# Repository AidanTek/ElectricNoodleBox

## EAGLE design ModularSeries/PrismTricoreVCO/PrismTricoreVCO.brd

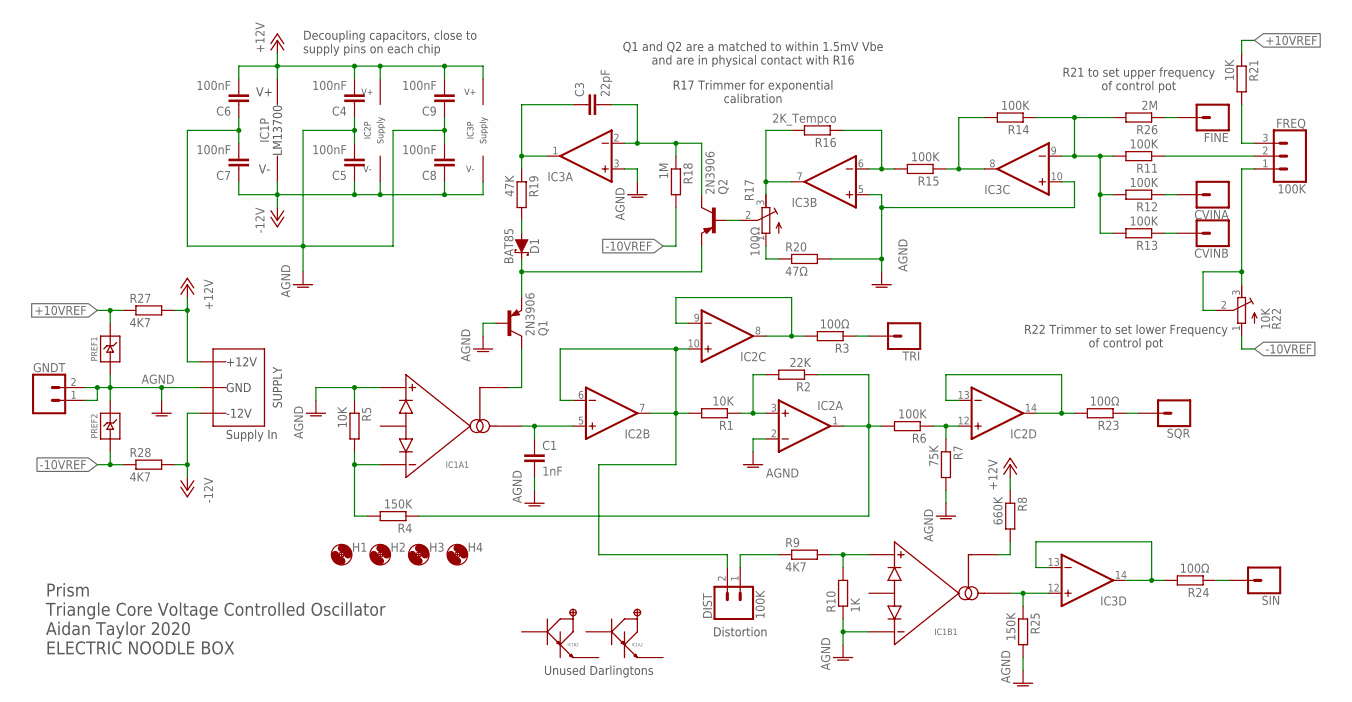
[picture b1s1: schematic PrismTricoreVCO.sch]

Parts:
C1: 1nF; C050-025X075
C3: 22pF; C050-025X075
C4, C5, C6, C7, C8, C9: 100nF; C050-025X075
CVINA: 1XWIREPAD; 1X01
CVINB: 1XWIREPAD; 1X01
D1: BAT85; DO35-7
DIST: 100K; 1X02
FINE: 1XWIREPAD; 1X01
FREQ: 100K; 1X03
GNDT: 2XWIREPAD; 1X02
H1, H2, H3, H4: MOUNT-HOLE3.2; 3,2
IC1: LM13700DIL; DIL16
IC2, IC3: TL0X4DIL; DIL14
PREF1, PREF2: LM4040TH; TO92
Q1, Q2: 2N3906; TO92
R1, R5, R21: 10K; 0207/10
R2: 22K; 0207/10
R3, R23, R24: 100Ω; 0207/10
R4, R25: 150K; 0207/10
R6, R11, R12, R13, R14, R15: 100K; 0207/10
R7: 75K; 0207/10
R8: 660K; 0207/10
R9, R27, R28: 4K7; 0207/10
R10: 1K; 0207/10
R16: 2K_Tempco; 0207/10
R17: 100Ω; RTRIM3296W
R18: 1M; 0207/10
R19: 47K; 0207/10
R20: 47Ω; 0207/10
R22: 10K; RTRIM3296W
R26: 2M; 0207/10
SIN: 1XWIREPAD; 1X01
SQR: 1XWIREPAD; 1X01
TRI: 1XWIREPAD; 1X01
WP1: COMBO_SUPPLY_HEADER; COMBINED_POWER

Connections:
+10VREF: PREF1.2 (CATHODE), R21.1, R27.1
+12V: C4.2, C6.2, C9.2, IC1.11 (V+), IC2.4 (V+), IC3.4 (V+), R8.1, R27.2, WP1.V+1 (V++), WP1.V+2 (V++), WP1.V+3 (V++)
-10VREF: PREF2.3 (ANODE), R18.2, R22.1 (A), R28.1
-12V: C5.1, C7.1, C8.1, IC1.6 (V-), IC2.11 (V-), IC3.11 (V-), R28.2, WP1.V-1 (V--), WP1.V-2 (V--), WP1.V-3 (V--)
AGND: C1.2, C4.1, C5.2, C6.1, C7.2, C8.2, C9.1, GNDT.1, GNDT.2, IC1.3 (AMP+), IC1.13 (AMP-), IC2.2 (-IN), IC3.3 (+IN), IC3.5 (+IN), IC3.10 (+IN), PREF1.3 (ANODE), PREF2.2 (CATHODE), Q1.2 (B), R5.1, R7.2, R10.1, R20.2, R25.2, WP1.GND1 (AGND), WP1.GND2 (AGND), WP1.GND3 (AGND), WP1.GND4 (AGND), WP1.GND5 (AGND), WP1.GND6 (AGND), WP1.GND7 (AGND), WP1.GND8 (AGND)
unnamed: DIST.2, IC2.6 (-IN), IC2.7 (OUT), IC2.10 (+IN), R1.2
unnamed: IC2.3 (+IN), R1.1, R2.2
unnamed: C1.1, IC1.5 (AMPOUT), IC2.5 (+IN)
unnamed: IC2.1 (OUT), R2.1, R4.1, R6.2
unnamed: IC2.8 (OUT), IC2.9 (-IN), R3.2
unnamed: IC1.4 (AMP-), R4.2, R5.2
unnamed: IC1.14 (AMP+), R9.2, R10.2
unnamed: IC2.12 (+IN), R6.1, R7.1
unnamed: IC1.12 (AMPOUT), IC3.12 (+IN), R25.1
unnamed: IC1.16 (AMPBIAS), R8.2
unnamed: IC1.1 (AMPBIAS), Q1.1 (C)
unnamed: DIST.1, R9.1
unnamed: IC3.7 (OUT), R16.2, R17.3 (E)
unnamed: IC3.6 (-IN), R15.2, R16.1
unnamed: IC3.8 (OUT), R14.2, R15.1
unnamed: Q2.2 (B), R17.2 (S)
unnamed: C3.2, IC3.2 (-IN), Q2.1 (C), R18.1
unnamed: R17.1 (A), R20.1
unnamed: C3.1, IC3.1 (OUT), R19.1
unnamed: D1.C, Q1.3 (E), Q2.3 (E)
unnamed: D1.A, R19.2
unnamed: IC3.9 (-IN), R11.2, R12.2, R13.2, R14.1, R26.2
unnamed: FREQ.2, R11.1
unnamed: FREQ.1, R22.2 (S), R22.3 (E)
unnamed: FREQ.3, R21.2
unnamed: CVINA.1, R12.1
unnamed: CVINB.1, R13.1
unnamed: R3.1, TRI.1
unnamed: R23.1, SQR.1
unnamed: R24.1, SIN.1
unnamed: FINE.1, R26.1
SINE_OUT: IC3.13 (-IN), IC3.14 (OUT), R24.2
SQUARE_OUT: IC2.13 (-IN), IC2.14 (OUT), R23.2

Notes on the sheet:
Distortion
Unused Darlingtons
R22 Trimmer to set lower Frequency of control pot
R17 Trimmer for exponential calibration
R21 to set upper frequency of control pot
Q1 and Q2 are a matched to within 1.5mV Vbe and are in physical contact with R16
Prism Triangle Core Voltage Controlled Oscillator Aidan Taylor 2020 ELECTRIC NOODLE BOX
Supply In
Decoupling capacitors, close to supply pins on each chip

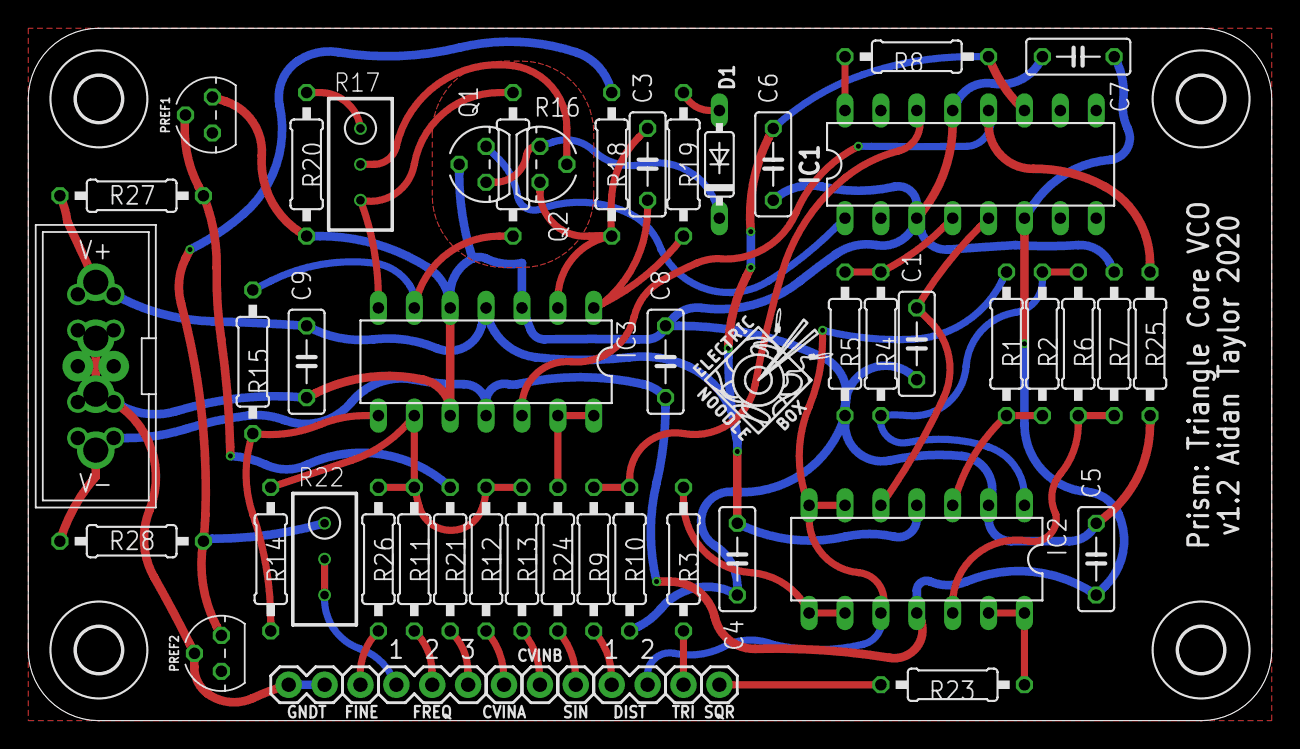
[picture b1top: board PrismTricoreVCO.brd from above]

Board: 2 copper layers, 88.0 x 49.0 mm, 60 parts (1 on the bottom side), 38 nets.

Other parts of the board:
U$1, U$2: LOGO10X10

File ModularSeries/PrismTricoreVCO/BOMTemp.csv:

"Qty";"Value";"Device";"Package";"Parts";"Description";"POPULARITY";"SPICEMODEL";"SPICEPREFIX";"SPICEPREFIXL";
"1";"";"LM13700DIL";"DIL16";"IC1";"";"";"";"";"";
"2";"";"LM4040TH";"TO-92";"PREF1, PREF2";"";"";"";"";"";
"2";"";"TL0X4DIL";"DIL14";"IC2, IC3";"";"";"";"";"";
"1";"100K";"2XWIREPAD";"1X02";"DIST";"";"";"";"";"";
"1";"100K";"3XWIREPAD";"1X03";"FREQ";"";"";"";"";"";
"6";"100K";"R-EU_0207/10";"0207/10";"R6, R11, R12, R13, R14, R15";"RESISTOR, European symbol";"81";"";"R";"";
"6";"100nF";"C-EU050-025X075";"C050-025X075";"C4, C5, C6, C7, C8, C9";"CAPACITOR, European symbol";"29";"";"C";"";
"3";"100Ω";"R-EU_0207/10";"0207/10";"R3, R23, R24";"RESISTOR, European symbol";"81";"";"R";"";
"1";"100Ω";"R-TRIMM3296W";"RTRIM3296W";"R17";"Trimm resistor";"3";"X";"";"POT";
"3";"10K";"R-EU_0207/10";"0207/10";"R1, R5, R21";"RESISTOR, European symbol";"81";"";"R";"";
"1";"10K";"R-TRIMM3296W";"RTRIM3296W";"R22";"Trimm resistor";"3";"X";"";"POT";
"2";"150K";"R-EU_0207/10";"0207/10";"R4, R25";"RESISTOR, European symbol";"81";"";"R";"";
"1";"1K";"R-EU_0207/10";"0207/10";"R10";"RESISTOR, European symbol";"81";"";"R";"";
"1";"1M";"R-EU_0207/10";"0207/10";"R18";"RESISTOR, European symbol";"81";"";"R";"";
"6";"1XWIREPAD";"1XWIREPAD";"1X01";"CVINA, CVINB, FINE, SIN, SQR, TRI";"";"";"";"";"";
"1";"1nF";"C-EU050-025X075";"C050-025X075";"C1";"CAPACITOR, European symbol";"29";"";"C";"";
"1";"22K";"R-EU_0207/10";"0207/10";"R2";"RESISTOR, European symbol";"81";"";"R";"";
"1";"22pF";"C-EU050-025X075";"C050-025X075";"C3";"CAPACITOR, European symbol";"29";"";"C";"";
"1";"2K_Tempco";"R-EU_0207/10";"0207/10";"R16";"RESISTOR, European symbol";"81";"";"R";"";
"1";"2M";"R-EU_0207/10";"0207/10";"R26";"RESISTOR, European symbol";"81";"";"R";"";
"2";"2N3906";"2N3906";"TO92";"Q1, Q2";"PNP Transistor";"11";"";"";"";
"1";"2XWIREPAD";"2XWIREPAD";"1X02";"GNDT";"";"";"";"";"";
"1";"47K";"R-EU_0207/10";"0207/10";"R19";"RESISTOR, European symbol";"81";"";"R";"";
"1";"47Ω";"R-EU_0207/10";"0207/10";"R20";"RESISTOR, European symbol";"81";"";"R";"";
"3";"4K7";"R-EU_0207/10";"0207/10";"R9, R27, R28";"RESISTOR, European symbol";"81";"";"R";"";
"1";"660K";"R-EU_0207/10";"0207/10";"R8";"RESISTOR, European symbol";"81";"";"R";"";
"1";"75K";"R-EU_0207/10";"0207/10";"R7";"RESISTOR, European symbol";"81";"";"R";"";
"1";"BAT85";"SCHOTTKY_DO35";"DO35-7";"D1";"";"";"";"";"";
"1";"COMBO_SUPPLY_HEADER";"COMBO_SUPPLY_HEADER";"COMBINED_POWER";"WP1";"";"";"";"";"";
"4";"MOUNT-HOLE3.2";"MOUNT-HOLE3.2";"3,2";"H1, H2, H3, H4";"MOUNTING HOLE with drill center marker";"7";"";"";"";

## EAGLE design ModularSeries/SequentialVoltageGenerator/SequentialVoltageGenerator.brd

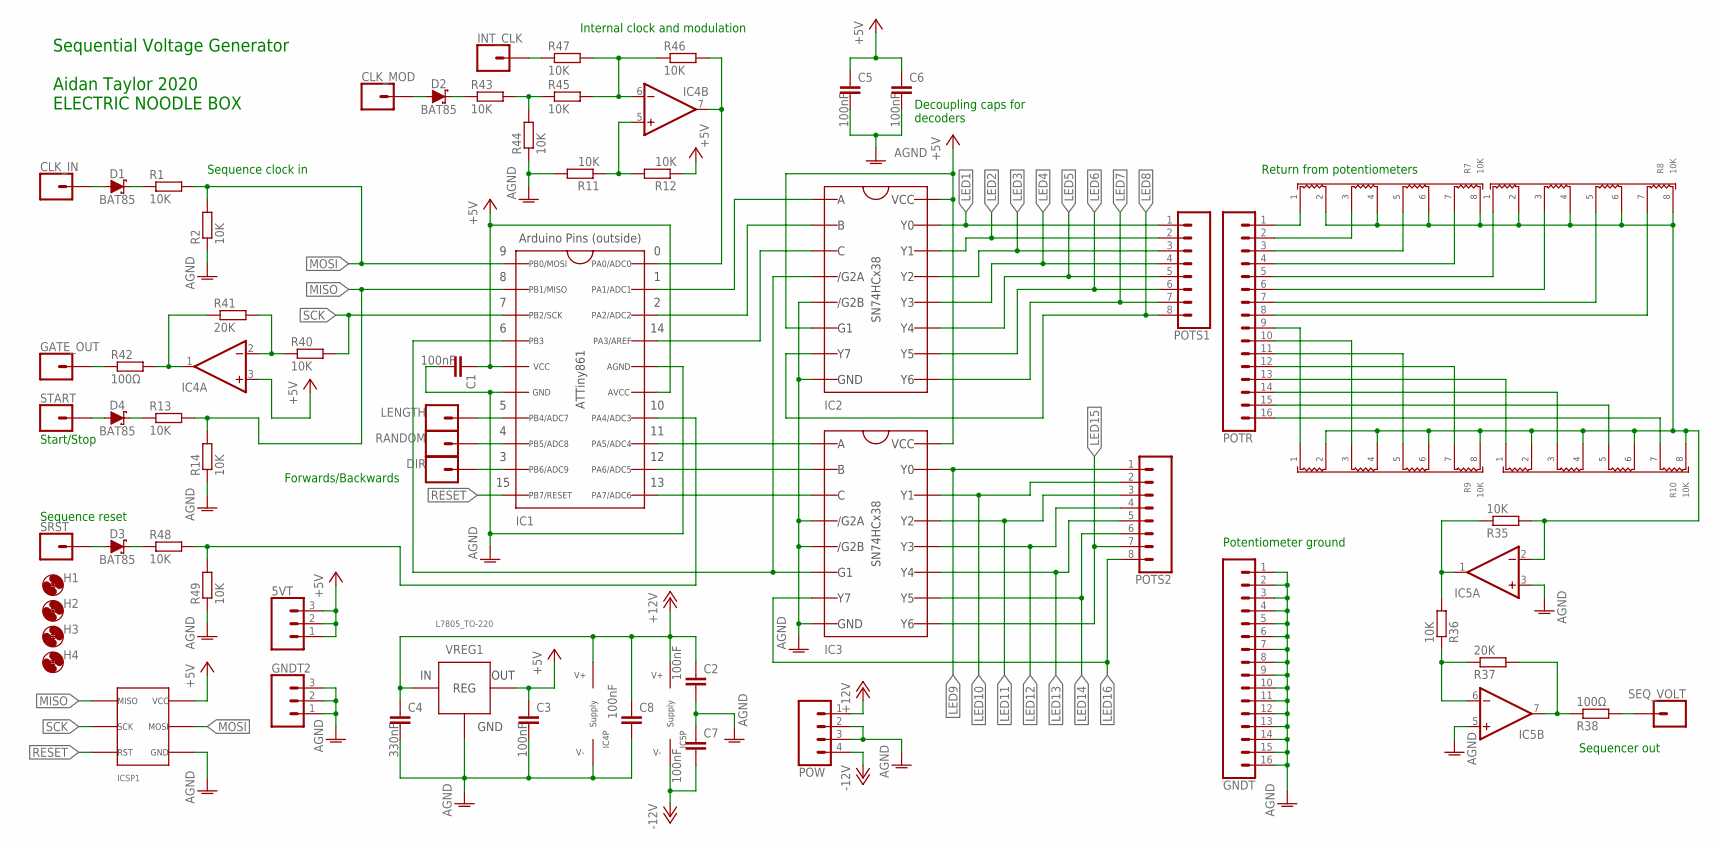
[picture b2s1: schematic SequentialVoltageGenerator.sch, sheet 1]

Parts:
5VT: 3XWIREPAD; 1X03
C1, C2, C3, C5, C6, C7, C8: 100nF; C050-025X075
C4: 330nF; C050-025X075
CLK_IN: 1XWIREPAD; 1X01
CLK_MOD: 1XWIREPAD; 1X01
D1, D2, D3, D4: BAT85; DO35-7
DIR: 1XWIREPAD; 1X01
GATE_OUT: 1XWIREPAD; 1X01
GNDT: 16XWIREPAD; 1X16
GNDT2: 3XWIREPAD; 1X03
H1, H2, H3, H4: MOUNT-HOLE3.2; 3,2
IC1: ATTINY861_DIP; DIL20
IC2, IC3: SN74HCX38; DIL16
IC4: LM358_DIP; DIL08
IC5: TL0X2_DIP; DIL08
ICSP1: ICSP_2.54; 2X3
INT_CLK: 1XWIREPAD; 1X01
LENGTH: 1XWIREPAD; 1X01
POTR: 16XWIREPAD; 1X16
POTS1, POTS2: 8XWIREPAD; 1X08
POW: 4XMOLEX; MOLEX-1X4
R1, R2, R11, R12, R13, R14, R35, R36, R40, R43, R44, R45, R46, R47, R48, R49: 10K; 0207/10
R7, R8, R9, R10: 10K; 4_ISO_RES_NET_2.54
R37, R41: 20K; 0207/10
R38, R42: 100Ω; 0207/10
RANDOM: 1XWIREPAD; 1X01
SEQ_VOLT: 1XWIREPAD; 1X01
SRST: 1XWIREPAD; 1X01
START: 1XWIREPAD; 1X01
VREG1: L7805_TO-220; TO220H

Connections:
+5V: 5VT.1, 5VT.2, 5VT.3, C1.1, C3.1, C5.1, C6.1, IC1.5 (VCC), IC1.15 (AVCC), IC2.6 (6_G1), IC2.16 (16_VCC), IC3.16 (16_VCC), IC4.3 (+IN), ICSP1.2 (6VCC), R12.1, VREG1.3 (VOUT); also elsewhere on the board
+12V: C2.1, C4.1, C8.1, IC4.8 (V+), IC5.8 (V+), POW.1, VREG1.1 (VIN)
-12V: C7.2, IC5.4 (V-), POW.4
AGND: C1.2, C2.2, C3.2, C4.2, C5.2, C6.2, C7.1, C8.2, GNDT.1, GNDT.2, GNDT.3, GNDT.4, GNDT.5, GNDT.6, GNDT.7, GNDT.8, GNDT.9, GNDT.10, GNDT.11, GNDT.12, GNDT.13, GNDT.14, GNDT.15, GNDT.16, GNDT2.1, GNDT2.2, GNDT2.3, IC1.6 (GND), IC1.16 (AGND), IC2.5 (5_/G2B), IC2.8 (8_GND), IC3.4 (4_/G2A), IC3.5 (5_/G2B), IC3.8 (8_GND), IC4.4 (V-), IC5.3 (+IN), IC5.5 (+IN), ICSP1.6 (4GND), POW.2, POW.3, R2.1, R11.2, R14.1, R44.1, R49.1, VREG1.2 (GND); also elsewhere on the board
LED1: IC2.15 (15_Y0), POTS1.1; also elsewhere on the board
LED2: IC2.14 (14_Y1), POTS1.2; also elsewhere on the board
LED3: IC2.13 (13_Y2), POTS1.3; also elsewhere on the board
LED4: IC2.12 (12_Y3), POTS1.4; also elsewhere on the board
LED5: IC2.11 (11_Y4), POTS1.5; also elsewhere on the board
LED6: IC2.10 (10_Y5), POTS1.6; also elsewhere on the board
LED7: IC2.9 (9_Y6), POTS1.7; also elsewhere on the board
LED8: IC2.7 (7_Y7), POTS1.8; also elsewhere on the board
LED9: IC3.15 (15_Y0), POTS2.1; also elsewhere on the board
LED10: IC3.14 (14_Y1), POTS2.2; also elsewhere on the board
LED11: IC3.13 (13_Y2), POTS2.3; also elsewhere on the board
LED12: IC3.12 (12_Y3), POTS2.4; also elsewhere on the board
LED13: IC3.11 (11_Y4), POTS2.5; also elsewhere on the board
LED14: IC3.10 (10_Y5), POTS2.6; also elsewhere on the board
LED15: IC3.9 (9_Y6), POTS2.7; also elsewhere on the board
LED16: IC3.7 (7_Y7), POTS2.8; also elsewhere on the board
MISO: IC1.2 (2_PB1), ICSP1.1 (1MISO), R13.2, R14.2
MOSI: IC1.1 (1_PB0), ICSP1.4 (5MOSI), R1.2, R2.2
unnamed: IC1.4 (4_PB3), IC2.4 (4_/G2A), IC3.6 (6_G1)
unnamed: IC1.17 (17_PA3), IC2.3 (3_C)
unnamed: IC1.18 (18_PA2), IC2.2 (2_B)
unnamed: IC1.19 (19_PA1), IC2.1 (1_A)
unnamed: D4.A, START.1
unnamed: IC1.12 (12_PA6), IC3.2 (2_B)
unnamed: IC1.11 (11_PA7), IC3.3 (3_C)
unnamed: CLK_IN.1, D1.A
unnamed: D1.C, R1.1
unnamed: POTR.1, R7.P$1
unnamed: POTR.2, R7.P$3
unnamed: POTR.3, R7.P$5
unnamed: POTR.4, R7.P$7
unnamed: POTR.5, R8.P$1
unnamed: POTR.6, R8.P$3
unnamed: POTR.7, R8.P$5
unnamed: POTR.8, R8.P$7
unnamed: POTR.9, R9.P$1
unnamed: POTR.10, R9.P$3
unnamed: POTR.11, R9.P$5
unnamed: POTR.12, R9.P$7
unnamed: POTR.13, R10.P$1
unnamed: POTR.14, R10.P$3
unnamed: POTR.15, R10.P$5
unnamed: POTR.16, R10.P$7
unnamed: IC5.2 (-IN), R7.P$2, R7.P$4, R7.P$6, R7.P$8, R8.P$2, R8.P$4, R8.P$6, R8.P$8, R9.P$2, R9.P$4, R9.P$6, R9.P$8, R10.P$2, R10.P$4, R10.P$6, R10.P$8, R35.2
unnamed: IC5.1 (OUT), R35.1, R36.2
unnamed: IC5.6 (-IN), R36.1, R37.1
unnamed: R38.2, SEQ_VOLT.1
unnamed: IC5.7 (OUT), R37.2, R38.1
unnamed: IC4.2 (-IN), R40.1, R41.2
unnamed: GATE_OUT.1, R42.1
unnamed: IC4.1 (OUT), R41.1, R42.2
unnamed: D2.C, R43.1
unnamed: R43.2, R44.2, R45.1
unnamed: IC4.6 (-IN), R45.2, R46.1, R47.2
unnamed: IC1.20 (20_PA0), IC4.7 (OUT), R46.2
unnamed: INT_CLK.1, R47.1
unnamed: CLK_MOD.1, D2.A
unnamed: IC1.7 (7_PB4), LENGTH.1
unnamed: IC1.8 (8_PB5), RANDOM.1
unnamed: DIR.1, IC1.9 (9_PB6)
unnamed: D3.A, SRST.1
unnamed: D3.C, R48.1
unnamed: IC1.14 (14_PA4), R48.2, R49.2
unnamed: IC4.5 (+IN), R11.1, R12.2
unnamed: IC1.13 (13_PA5), IC3.1 (1_A)
unnamed: D4.C, R13.1
RESET: IC1.10 (10_PB7), ICSP1.5 (3RST)
SCK: IC1.3 (3_PB2), ICSP1.3 (2SCK), R40.2

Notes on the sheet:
Decoupling caps for decoders
Sequence reset
Start/Stop
Sequence clock in
Internal clock and modulation
Potentiometer ground
Sequencer out
Return from potentiometers
Sequential Voltage Generator Aidan Taylor 2020 ELECTRIC NOODLE BOX
Forwards/Backwards

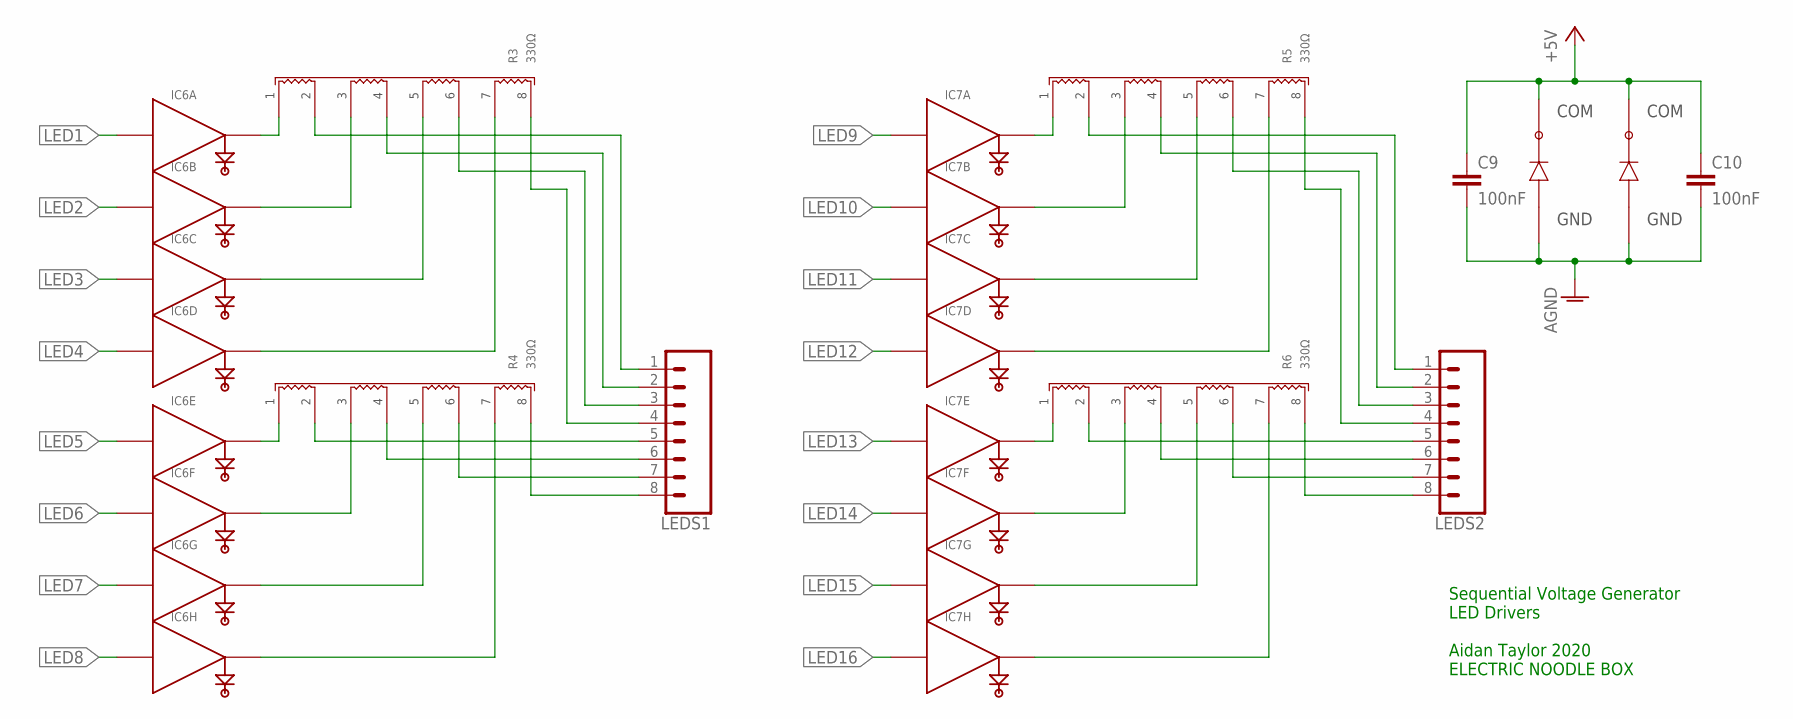
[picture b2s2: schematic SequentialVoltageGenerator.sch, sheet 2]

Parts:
C9, C10: 100nF; C050-025X075
IC6, IC7: ULN2801_DIP; DIL18
LEDS1, LEDS2: 8XWIREPAD; 1X08
R3, R4, R5, R6: 330Ω; 4_ISO_RES_NET_2.54

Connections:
+5V: C9.1, C10.1, IC6.10 (COM), IC7.10 (COM); also elsewhere on the board
AGND: C9.2, C10.2, IC6.9 (GND), IC7.9 (GND); also elsewhere on the board
LED1: IC6.1 (IN); also elsewhere on the board
LED2: IC6.2 (IN); also elsewhere on the board
LED3: IC6.3 (IN); also elsewhere on the board
LED4: IC6.4 (IN); also elsewhere on the board
LED5: IC6.5 (IN); also elsewhere on the board
LED6: IC6.6 (IN); also elsewhere on the board
LED7: IC6.7 (IN); also elsewhere on the board
LED8: IC6.8 (IN); also elsewhere on the board
LED9: IC7.1 (IN); also elsewhere on the board
LED10: IC7.2 (IN); also elsewhere on the board
LED11: IC7.3 (IN); also elsewhere on the board
LED12: IC7.4 (IN); also elsewhere on the board
LED13: IC7.5 (IN); also elsewhere on the board
LED14: IC7.6 (IN); also elsewhere on the board
LED15: IC7.7 (IN); also elsewhere on the board
LED16: IC7.8 (IN); also elsewhere on the board
unnamed: IC6.18, R3.P$1
unnamed: LEDS1.1, R3.P$2
unnamed: IC6.17, R3.P$3
unnamed: LEDS1.2, R3.P$4
unnamed: IC6.16, R3.P$5
unnamed: LEDS1.3, R3.P$6
unnamed: IC6.15, R3.P$7
unnamed: LEDS1.4, R3.P$8
unnamed: IC6.14, R4.P$1
unnamed: LEDS1.5, R4.P$2
unnamed: IC6.13, R4.P$3
unnamed: LEDS1.6, R4.P$4
unnamed: IC6.12, R4.P$5
unnamed: LEDS1.7, R4.P$6
unnamed: IC6.11, R4.P$7
unnamed: LEDS1.8, R4.P$8
unnamed: IC7.18, R5.P$1
unnamed: LEDS2.1, R5.P$2
unnamed: IC7.17, R5.P$3
unnamed: LEDS2.2, R5.P$4
unnamed: IC7.16, R5.P$5
unnamed: LEDS2.3, R5.P$6
unnamed: IC7.15, R5.P$7
unnamed: LEDS2.4, R5.P$8
unnamed: IC7.14, R6.P$1
unnamed: LEDS2.5, R6.P$2
unnamed: IC7.13, R6.P$3
unnamed: LEDS2.6, R6.P$4
unnamed: IC7.12, R6.P$5
unnamed: LEDS2.7, R6.P$6
unnamed: IC7.11, R6.P$7
unnamed: LEDS2.8, R6.P$8

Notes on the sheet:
Sequential Voltage Generator LED Drivers Aidan Taylor 2020 ELECTRIC NOODLE BOX

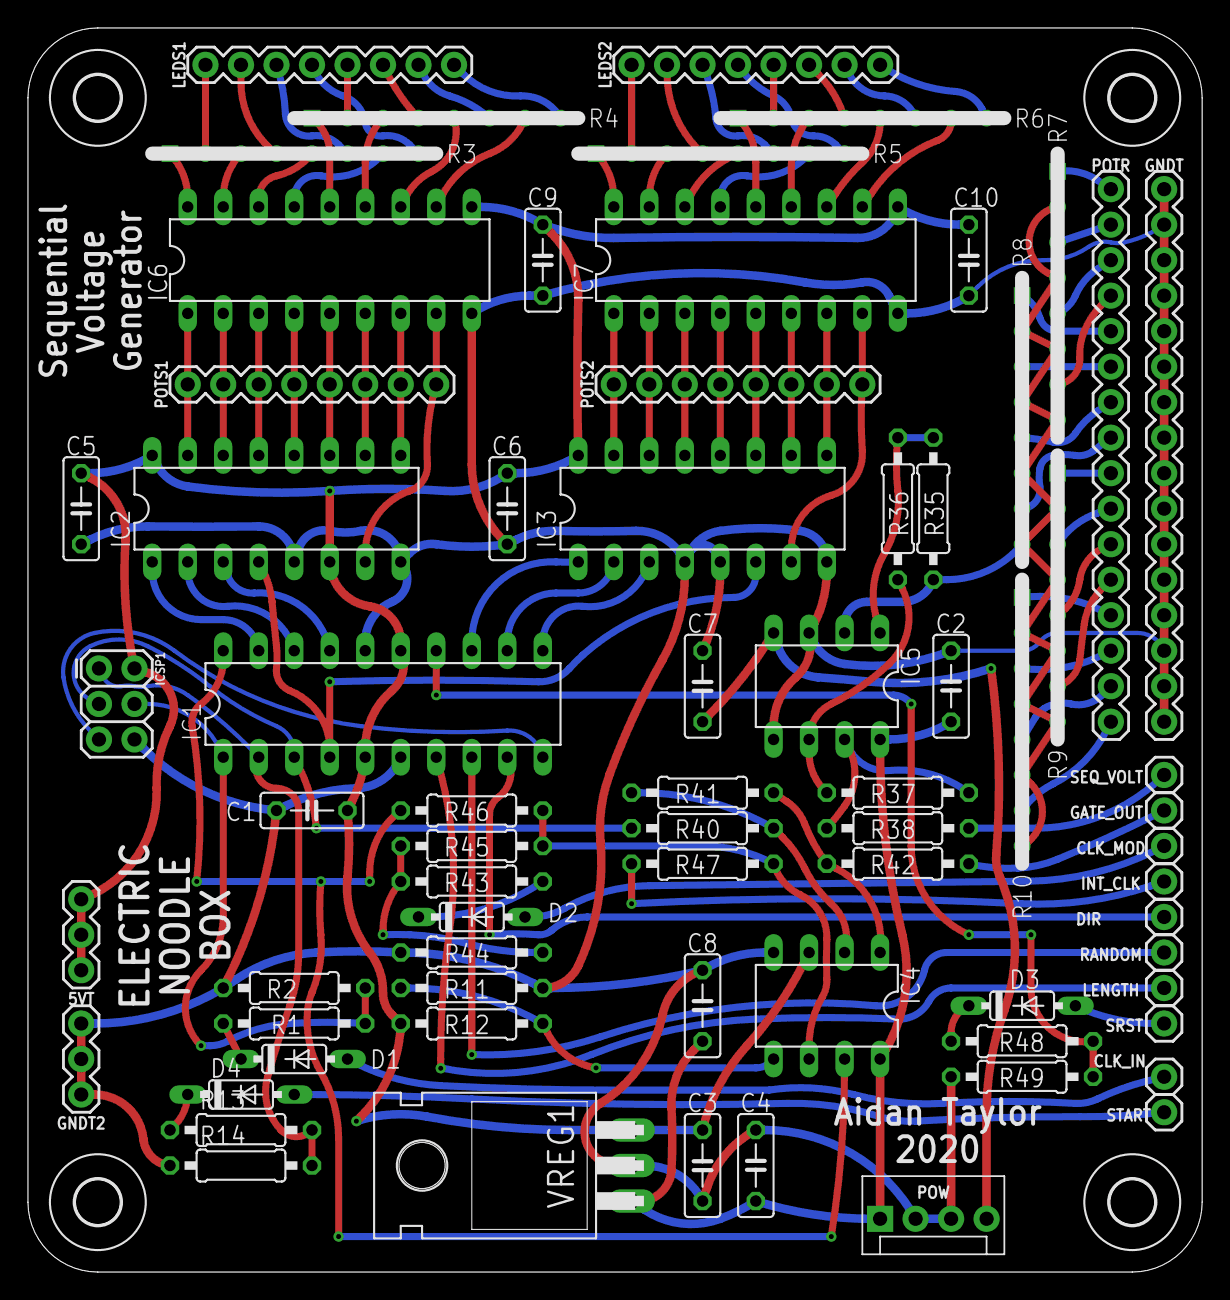
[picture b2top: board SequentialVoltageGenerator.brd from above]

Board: 2 copper layers, 84.0 x 89.0 mm, 74 parts (0 on the bottom side), 104 nets.

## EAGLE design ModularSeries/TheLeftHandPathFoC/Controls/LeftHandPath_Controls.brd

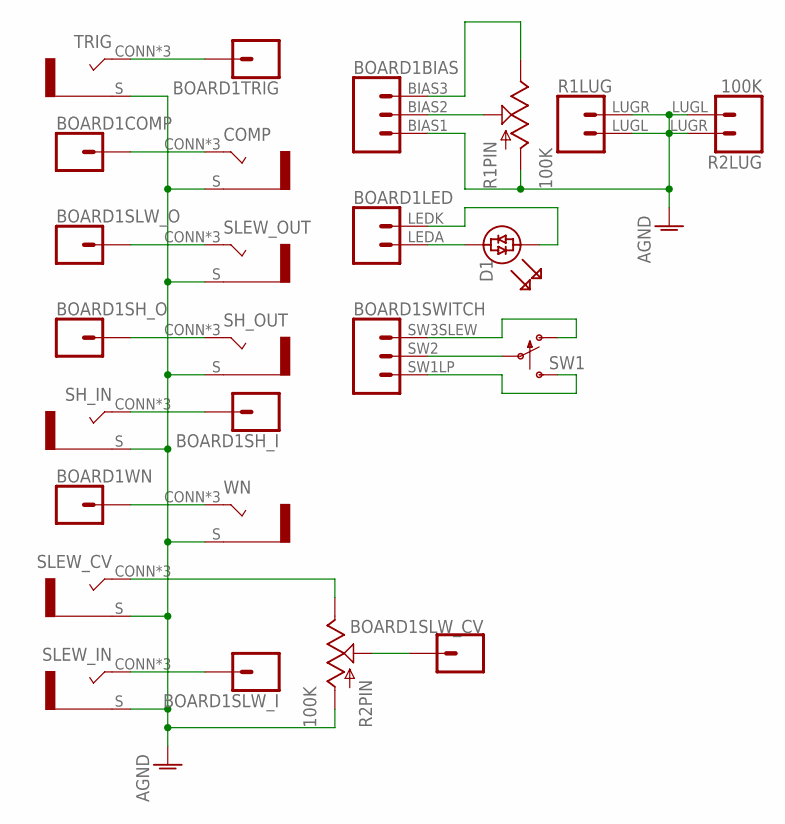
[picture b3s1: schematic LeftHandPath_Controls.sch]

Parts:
BOARD1: TLHPFOC_LINK; TLHPFOC
COMP: COMBI-JACKCINCHNANA; NEWCOMBOJACK_PANEL
D1: 5MM_BICOLOUR_LED; LED5MM
R1, R2: 100K; ALPHA_RV09_9MMPOT
SH_IN: COMBI-JACKCINCHNANA; NEWCOMBOJACK_PANEL
SH_OUT: COMBI-JACKCINCHNANA; NEWCOMBOJACK_PANEL
SLEW_CV: COMBI-JACKCINCHNANA; NEWCOMBOJACK_PANEL
SLEW_IN: COMBI-JACKCINCHNANA; NEWCOMBOJACK_PANEL
SLEW_OUT: COMBI-JACKCINCHNANA; NEWCOMBOJACK_PANEL
SW1: SPDT_SWITCHDW1; MICRODPDT-DW1
TRIG: COMBI-JACKCINCHNANA; NEWCOMBOJACK_PANEL
WN: COMBI-JACKCINCHNANA; NEWCOMBOJACK_PANEL

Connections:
AGND: BOARD1.BIAS1 (1), COMP.S, R1.C1 (A), R1.LUGL (1), R1.LUGR (2), R2.C1 (A), R2.LUGL (1), R2.LUGR (2), SH_IN.S, SH_OUT.S, SLEW_CV.S, SLEW_IN.S, SLEW_OUT.S, TRIG.S, WN.S
unnamed: BOARD1.TRIG (1), TRIG.CONN (T), TRIG.T1 (T), TRIG.T2 (T)
unnamed: BOARD1.COMP (1), COMP.CONN (T), COMP.T1 (T), COMP.T2 (T)
unnamed: BOARD1.SLW_O (1), SLEW_OUT.CONN (T), SLEW_OUT.T1 (T), SLEW_OUT.T2 (T)
unnamed: BOARD1.SH_O (1), SH_OUT.CONN (T), SH_OUT.T1 (T), SH_OUT.T2 (T)
unnamed: BOARD1.SH_I (1), SH_IN.CONN (T), SH_IN.T1 (T), SH_IN.T2 (T)
unnamed: BOARD1.WN (1), WN.CONN (T), WN.T1 (T), WN.T2 (T)
unnamed: BOARD1.BIAS2 (2), R1.C2 (W)
unnamed: BOARD1.LEDA (1), D1.A (AN)
unnamed: BOARD1.LEDK (2), D1.K (KA)
unnamed: BOARD1.SLW_I (1), SLEW_IN.CONN (T), SLEW_IN.T1 (T), SLEW_IN.T2 (T)
unnamed: R2.C3 (B), SLEW_CV.CONN (T), SLEW_CV.T1 (T), SLEW_CV.T2 (T)
unnamed: BOARD1.BIAS3 (3), R1.C3 (B)
unnamed: BOARD1.SW2 (2), SW1.C2
unnamed: BOARD1.SW3SLEW (3), SW1.C1 (O)
unnamed: BOARD1.SW1LP (1), SW1.C3 (S)
unnamed: BOARD1.SLW_CV (1), R2.C2 (W)

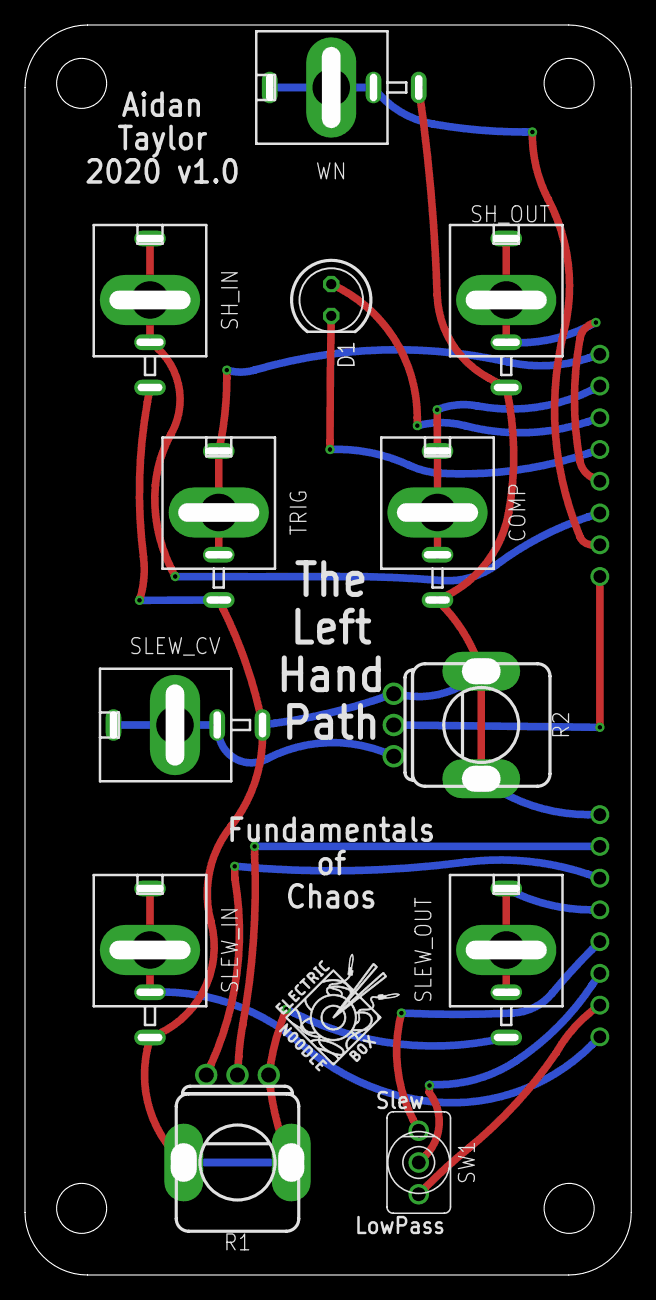
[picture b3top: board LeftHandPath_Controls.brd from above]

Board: 2 copper layers, 48.5 x 100.0 mm, 14 parts (1 on the bottom side), 17 nets.

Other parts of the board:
U$1: LOGO10X10

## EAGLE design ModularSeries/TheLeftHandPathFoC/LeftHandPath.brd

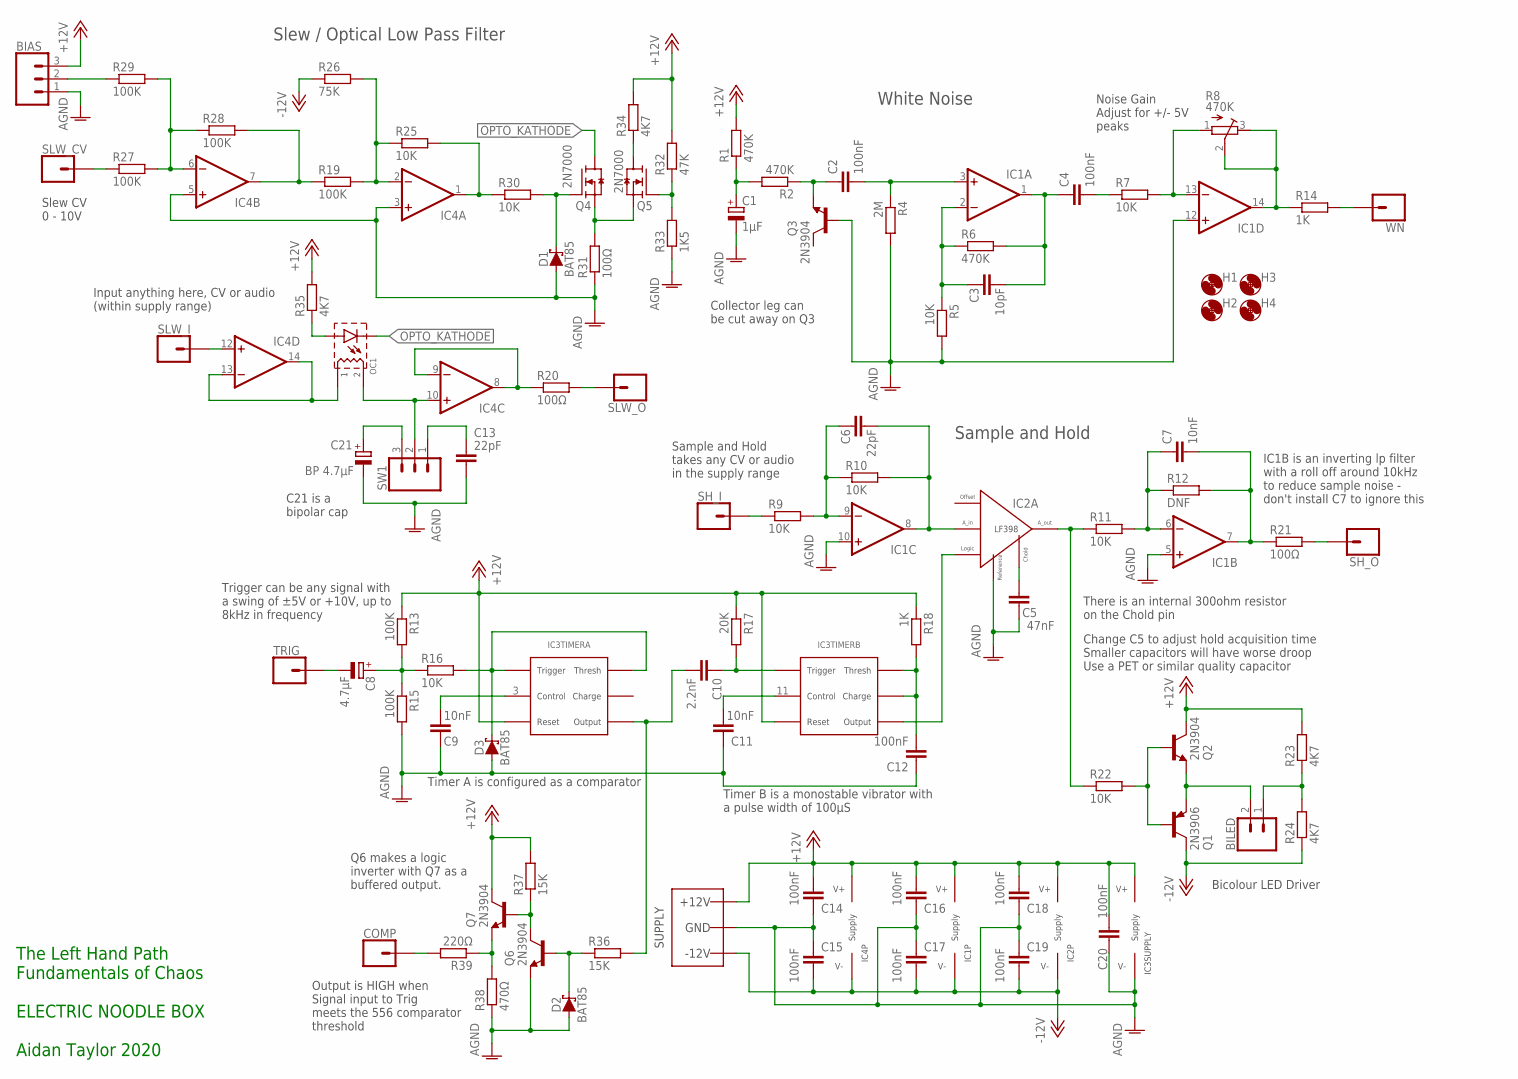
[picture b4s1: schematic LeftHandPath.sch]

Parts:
BIAS: 3XWIREPAD; 1X03
BILED: 2XWIREPAD; 1X02
C1: 1µF; E2-5
C2, C4, C12, C14, C15, C16, C17, C18, C19, C20: 100nF; C050-025X075
C3: 10pF; C050-025X075
C5: 47nF; C050-025X075
C6, C13: 22pF; C050-025X075
C7, C9, C11: 10nF; C050-025X075
C8: 4.7µF; E2-5
C10: 2.2nF; C050-025X075
C21: BP 4.7µF; E2-5
COMP: 1XWIREPAD; 1X01
D1, D2, D3: BAT85; DO35-7
H1, H2, H3, H4: MOUNT-HOLE3.2; 3,2
IC1, IC4: TL0X4DIL; DIL14
IC2: LF398; DIL08
IC3: 556_DUALTIMERDIL14; DIL14
OC1: OPTOCOUPLERSILONEX; SILONEX_OPTOCOUPLER
Q1: 2N3906; TO92
Q2, Q3, Q6, Q7: 2N3904; TO92
Q4, Q5: 2N7000; TO92
R1, R2, R6: 470K; 0207/7
R4: 2M; 0207/7
R5, R7, R9, R10, R11, R16, R22, R25, R30: 10K; 0207/7
R8: 470K; RTRIM3296W
R12: DNF; 0207/7
R13, R15, R19, R27, R28, R29: 100K; 0207/7
R14, R18: 1K; 0207/7
R17: 20K; 0207/7
R20, R21, R31: 100Ω; 0207/7
R23, R24, R34, R35: 4K7; 0207/7
R26: 75K; 0207/7
R32: 47K; 0207/7
R33: 1K5; 0207/7
R36, R37: 15K; 0207/7
R38: 470Ω; 0207/7
R39: 220Ω; 0207/7
SH_I: 1XWIREPAD; 1X01
SH_O: 1XWIREPAD; 1X01
SLW_CV: 1XWIREPAD; 1X01
SLW_I: 1XWIREPAD; 1X01
SLW_O: 1XWIREPAD; 1X01
SW1: 3XWIREPAD; 1X03
TRIG: 1XWIREPAD; 1X01
WN: 1XWIREPAD; 1X01
WP1: COMBO_SUPPLY_HEADER; COMBINED_POWER

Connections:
+12V: BIAS.3, C14.2, C16.2, C18.2, C20.2, IC1.4 (V+), IC2.1 (V+), IC3.4 (RESET), IC3.10 (RESET), IC3.14 (V+), IC4.4 (V+), Q2.1 (C), Q7.1 (C), R1.2, R13.1, R17.1, R18.1, R23.2, R32.2, R34.2, R35.2, R37.2, WP1.V+1 (V++), WP1.V+2 (V++), WP1.V+3 (V++)
-12V: C15.1, C17.1, C19.1, IC1.11 (V-), IC2.4 (V-), IC4.11 (V-), Q1.1 (C), R24.1, R26.1, WP1.V-1 (V--), WP1.V-2 (V--), WP1.V-3 (V--)
AGND: BIAS.1, C1.-, C5.1, C9.1, C11.1, C12.1, C13.1, C14.1, C15.2, C16.1, C17.2, C18.1, C19.2, C20.1, C21.-, D1.A, D2.A, D3.A, IC1.5 (+IN), IC1.10 (+IN), IC1.12 (+IN), IC2.7 (REFERENCE), IC3.7 (V-), IC4.3 (+IN), IC4.5 (+IN), Q3.2 (B), Q6.3 (E), R4.2, R5.2, R15.2, R31.1, R33.1, R38.1, WP1.GND1 (AGND), WP1.GND2 (AGND), WP1.GND3 (AGND), WP1.GND4 (AGND), WP1.GND5 (AGND), WP1.GND6 (AGND), WP1.GND7 (AGND), WP1.GND8 (AGND)
unnamed: C1.+, R1.1, R2.2
unnamed: C2.1, Q3.3 (E), R2.1
unnamed: C2.2, IC1.3 (+IN), R4.1
unnamed: C3.1, IC1.2 (-IN), R5.1, R6.1
unnamed: C3.2, C4.1, IC1.1 (OUT), R6.2
unnamed: C4.2, R7.1
unnamed: IC1.13 (-IN), R7.2, R8.1 (A)
unnamed: IC1.14 (OUT), R8.2 (S), R8.3 (E), R14.1
unnamed: C6.1, IC1.9 (-IN), R9.2, R10.1
unnamed: C6.2, IC1.8 (OUT), IC2.3 (ANALOG_IN), R10.2
unnamed: C5.2, IC2.6 (CH)
unnamed: IC2.5 (ANALOG_OUT), R11.1, R22.1
unnamed: C7.1, IC1.6 (-IN), R11.2, R12.1
unnamed: C7.2, IC1.7 (OUT), R12.2, R21.1
unnamed: R9.1, SH_I.1
unnamed: C10.2, IC3.5 (OUTPUT), R36.2
unnamed: C8.+, R13.2, R15.1, R16.1
unnamed: D3.C, IC3.2 (THRESHOLD), IC3.6 (TRIGGER), R16.2
unnamed: R14.2, WN.1
unnamed: C9.2, IC3.3 (CONT)
unnamed: C10.1, IC3.8 (TRIGGER), R17.2
unnamed: C11.2, IC3.11 (CONT)
unnamed: C12.2, IC3.12 (THRESHOLD), IC3.13 (DISCHARGE), R18.2
unnamed: IC2.8 (LOGIC), IC3.9 (OUTPUT)
unnamed: C8.-, TRIG.1
unnamed: IC4.12 (+IN), SLW_I.1
unnamed: IC4.13 (-IN), IC4.14 (OUT), OC1.1 (R1)
unnamed: IC4.7 (OUT), R19.1, R28.2
unnamed: IC4.10 (+IN), OC1.2 (R2), SW1.2
unnamed: C13.2, SW1.1
unnamed: R20.2, SLW_O.1
unnamed: R21.2, SH_O.1
unnamed: Q1.2 (B), Q2.2 (B), R22.2
unnamed: BILED.2, Q1.3 (E), Q2.3 (E)
unnamed: BILED.1, R23.1, R24.2
unnamed: IC4.2 (-IN), R19.2, R25.1, R26.2
unnamed: IC4.6 (-IN), R27.2, R28.1, R29.2
unnamed: IC4.1 (OUT), R25.2, R30.1
unnamed: D1.C, Q4.2 (G), R30.2
unnamed: Q4.1 (S), Q5.1 (S), R31.2
unnamed: C21.+, SW1.3
unnamed: Q5.2 (G), R32.1, R33.2
unnamed: Q5.3 (D), R34.1
unnamed: OC1.A, R35.1
unnamed: IC4.8 (OUT), IC4.9 (-IN), R20.1
unnamed: R27.1, SLW_CV.1
unnamed: BIAS.2, R29.1
unnamed: Q6.1 (C), Q7.2 (B), R37.1
unnamed: Q7.3 (E), R38.2, R39.1
unnamed: COMP.1, R39.2
unnamed: D2.C, Q6.2 (B), R36.1
OPTO_KATHODE: OC1.K, Q4.3 (D)

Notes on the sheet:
There is an internal 300ohm resistor on the Chold pin
Collector leg can be cut away on Q3
Noise Gain Adjust for +/- 5V peaks
Change C5 to adjust hold acquisition time Smaller capacitors will have worse droop Use a PET or similar quality capacitor
Timer A is configured as a comparator
Timer B is a monostable vibrator with a pulse width of 100µS
Trigger can be any signal with a swing of ±5V or +10V, up to 8kHz in frequency
IC1B is an inverting lp filter with a roll off around 10kHz to reduce sample noise - don't install C7 to ignore this
White Noise
Slew / Optical Low Pass Filter
Sample and Hold
Bicolour LED Driver
C21 is a bipolar cap
Q6 makes a logic inverter with Q7 as a buffered output.
Output is HIGH when Signal input to Trig meets the 556 comparator threshold
Slew CV 0 - 10V
Input anything here, CV or audio (within supply range)
Sample and Hold takes any CV or audio in the supply range
The Left Hand Path Fundamentals of Chaos ELECTRIC NOODLE BOX Aidan Taylor 2020

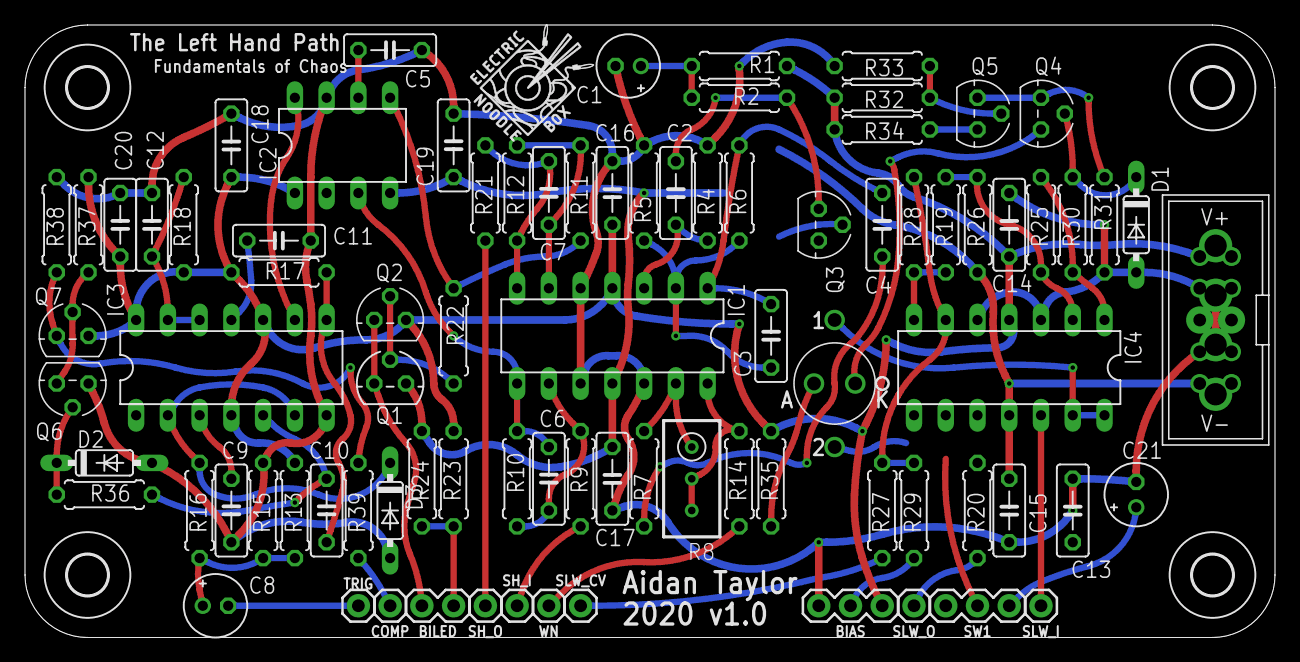
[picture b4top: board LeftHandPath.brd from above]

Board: 2 copper layers, 100.0 x 49.0 mm, 91 parts (0 on the bottom side), 55 nets.

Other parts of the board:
U$1: LOGO10X10

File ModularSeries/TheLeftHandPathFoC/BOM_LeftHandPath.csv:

Qty,Value,Package,Parts,Description,Retailer,Catalogue
,,,,,,
5,100K,0207/7,"R13, R15, R27, R28, R29",RESISTOR 1/4W,Farnell,2329853
3,100Ω,0207/7,"R14, R20, R21",RESISTOR 1/4W,Farnell,2329854
11,10K,0207/7,"R3, R5, R9, R10, R11, R16, R19, R22, R25, R30, R31",RESISTOR 1/4W,Farnell,2329855
3,15K,0207/7,"R33, R36, R37",RESISTOR 1/4W,Farnell,1563095
2,1K,0207/7,"R7, R18",RESISTOR 1/4W,Farnell,2329885
1,20K,0207/7,R17,RESISTOR 1/4W,Farnell,2329897
1,2M2,0207/7,R4,RESISTOR 1/4W,Farnell,1186239
1,220Ω,0207/7,R39,RESISTOR 1/4W,Farnell,2329900
3,470K,0207/7,"R1, R2, R6",RESISTOR 1/4W,Farnell,2329941
2,47K,0207/7,"R26, R32",RESISTOR 1/4W,Farnell,2329944
4,4K7,0207/7,"R23, R24, R34, R35",RESISTOR 1/4W,Farnell,2329947
1,470Ω,0207/7,R38,RESISTOR 1/4W,Farnell,2329942
1,100K,RTRIM3296W,R8,Trimm resistor Bourns 3296W,Farnell,9353194
,,,,,,
10,100nF,C050-025X075,"C2, C4, C12, C14, C15, C16, C17, C18, C19, C20",CAPACITOR Ceramic,Farnell,1141777
3,10nF,C050-025X075,"C7, C9, C11",CAPACITOR Ceramic,Farnell,2860090
1,10pF,C050-025X075,C3,CAPACITOR Ceramic,Farnell,2309022
1,1¬µF,E2-5,C1,CAPACITOR Electrolytic,Farnell,1236666
1,2.2nF,C050-025X075,C10,CAPACITOR Ceramic,Farnell,2860116
2,22pF,C050-025X075,"C6, C13",CAPACITOR Ceramic,Farnell,2860107
1,4.7¬µF,E2-5,C8,CAPACITOR Electrolytic,Farnell,9451234
1,47nF PET,C050-025X075,C5,CAPACITOR PET,Farnell,1006025
1,BP 4.7¬µF,E2-5,C21,CAPACITOR Bipolar Electrolytic,Farnell,1236668
,,,,,,
4,2N3904,TO92,"Q2, Q3, Q6, Q7",NPN TRANSISTOR,Farnell,1574370
1,2N3906,TO92,Q1,PNP Transistor,Farnell,1574372
2,2N7000,TO92,"Q4, Q5",N-Channel FET,Farnell,2453761
3,BAT85,DO35-7,"D1, D2, D3",DO35 Schottky Diode,Farnell,1097299
1,OPTOCOUPLERSILONEX,SILONEX_OPTOCOUPLER,OC1,Optocoupler NSL-32,Farnell,3168773
1,LF398,DIL08,IC2,LF398 Monolithic Sample and Hold 8-pin DIP,Farnell,3005404
2,TL084,DIL14,"IC1, IC4",TL084 Quad JFET Op-Amp 14-pin DIP,Farnell,3005140
1,556,DIL14,IC3,TLC556CN Timer ,Farnell,3121214
,,,,,,
1,COMBO_SUPPLY_HEADER,COMBINED_POWER,WP1,10 way Shrouded IDC,Farnell,2843527
,,,,,,
8,Banana Connector,,"SLW_CV, SLW_I, SLW_O, TRIG, COMP, SH_I, SH_0, WN",Banana or Jack patch point (panel part),Farnell,1698951
2,B100K Potentiometer,,"BIAS, SLW_CV",Taiwan Alpha 16mm (panel part),Rapid,65-0756
1,Switch,,SW1,Toggle switch SPDT (panel part),Farnell,9473491
